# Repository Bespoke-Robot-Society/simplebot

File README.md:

# SimpleBot

Bespoke Robot Society's original design for kids, students, or cost-sensitive tinkerers.

Goals:

* Control a basic, multipurpose teaching robot with the Pi Pico (or Pico W).
* Demonstrate **optical odometry** - measuring the distance wheels turn by counting pulses on light sensors.
* Demonstrate **line following** - steer the robot in response to reflectance sensors that give the position of the line.
* Leave pins open on the microcontroller for additional upgrades.
* **Do not exceed $20 in price, with batteries included.**

## Hardware

Simplebot is based on the "Arduino Smart Car" kit that can be found on Amazon or Aliexpress. This provides a caster wheel, two yellow "TT" motors with optical encoder wheels and actual wheels, a power switch, and a 4xAA battery case. (~$6)

For line detectors, a generic "Infrared Obstacle Avoidance Sensor" module can be found in the US for 20 for $10 - SimpleBot requires two ($1).

Microcontroller - Raspberry Pi Pico ($4) or Raspberry Pi Pico W ($6).

Motor Controller - The TB6612FNG dual H-bridge module. You might be able to find this for $1 or less from overseas, but 3 for $9 is available in the US. ($3)

The optical encoder module requires one LED, one photoresistor, five resistors, and one LM393 chip for both. I don't know the prices for these, as I had them on hand.

an MPU6050 (Accelerometer/gyroscope) and nRF24l01 (2.4GHz radio module) are included on the circuit board, but haven't been tested or programmed yet. These occupy the I2C and SPI buses respectively, and would play well with some additional sensors (at the cost of spare pins for more SPI devices).

## Circuit Board

A through-hole (THT) PCB design is available for easy assembly.

The PCB integrates:
- Raspberry Pi Pico microcontroller (or compatible)
- TB6612FNG motor driver (or external H-bridge support)
- Buck converter for power regulation
- LM393-based optical encoder circuit
- Headers for nRF24L01 radio and MPU6050 IMU
- 4 sensor headers for expansion
- Analog and digital GPIO breakouts

See [PCB_GUIDE.md](PCB_GUIDE.md) for detailed PCB documentation.

See [ASSEMBLY_GUIDE.md](ASSEMBLY_GUIDE.md) for mechanical assembly instructions. 

## Software

Copy the included files to your Pi Pico by USB cable. I used Thonny to test the robot's programs.

# Future Work

Should I switch to an off-the-shelf optical encoder module, or should I build a custom line detecting sensor?

Printed circuit boards:

* Through hole soldering kit
* a board-on-board PCB - same layout as the protoboard, but soldered flat together.
* a custom PCB that uses the ICs from the modules directly

SimpleBot is unfortunately too large for standard micromouse mazes, so a "simplebot mini" seems to be in order.

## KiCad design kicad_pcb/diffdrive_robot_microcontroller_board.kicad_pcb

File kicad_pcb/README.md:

Pico library: KiCad-RP-Pico-main

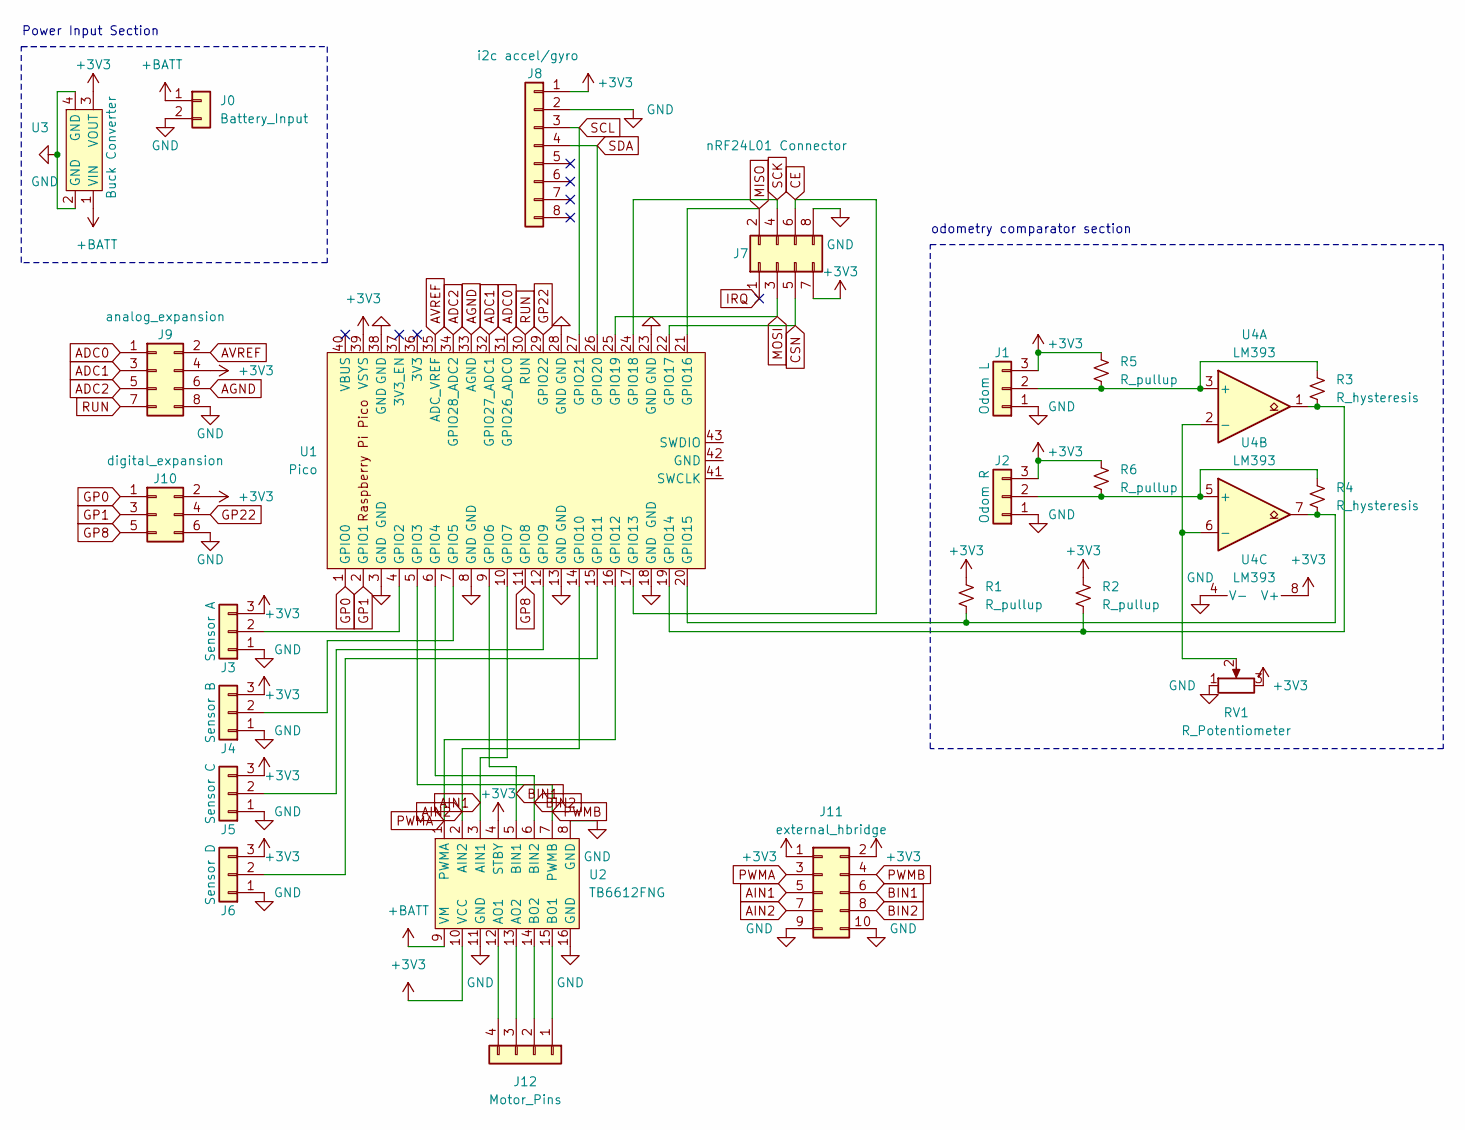
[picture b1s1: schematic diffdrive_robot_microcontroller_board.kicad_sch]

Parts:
J0: Battery_Input; PinSocket_1x02_P2.54mm_Vertical
J1: Odom L; PinHeader_1x03_P2.54mm_Vertical
J2: Odom R; PinHeader_1x03_P2.54mm_Vertical
J3: Sensor A; PinHeader_1x03_P2.54mm_Vertical
J4: Sensor B; PinHeader_1x03_P2.54mm_Vertical
J5: Sensor C; PinHeader_1x03_P2.54mm_Vertical
J6: Sensor D; PinHeader_1x03_P2.54mm_Vertical
J7: nRF24L01 Connector; PinSocket_2x04_P2.54mm_Vertical
J8: i2c accel/gyro; PinSocket_1x08_P2.54mm_Vertical
J9: analog_expansion; PinSocket_2x04_P2.54mm_Vertical
J10: digital_expansion; PinSocket_2x03_P2.54mm_Vertical
J11: external_hbridge; PinSocket_2x05_P2.54mm_Vertical
J12: Motor_Pins; PinSocket_1x04_P2.54mm_Vertical
R1, R2, R5, R6: R_pullup; R_Axial_DIN0207_L6.3mm_D2.5mm_P7.62mm_Horizontal
R3, R4: R_hysteresis; R_Axial_DIN0207_L6.3mm_D2.5mm_P7.62mm_Horizontal
RV1: R_Potentiometer; PinHeader_1x03_P2.54mm_Vertical
U1: Pico; RPi_Pico_SMD_TH
U2: TB6612FNG; TB6612FNG_Breakout
U3: Buck Converter; BuckConverter_Breakout
U4: LM393; DIP-8_W7.62mm_Socket

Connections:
+3V3: J1.3, J2.3, J3.3, J4.3, J5.3, J6.3, J7.7, J8.1, J9.4, J10.2, J11.1, J11.2, R1.1, R2.1, R5.1, R6.1, RV1.3, U1.39 (VSYS), U2.4 (STBY), U2.10 (VCC), U3.3 (VOUT), U4.8 (V+)
+BATT: J0.1, U2.9 (VM), U3.1 (VIN)
ADC0: J9.1, U1.31 (GPIO26_ADC0)
ADC1: J9.3, U1.32 (GPIO27_ADC1)
ADC2: J9.5, U1.34 (GPIO28_ADC2)
AGND: J9.6, U1.33 (AGND)
AIN1: J11.5, U1.10 (GPIO7), U2.3 (AIN1)
AIN2: J11.7, U1.14 (GPIO10), U2.2 (AIN2)
AVREF: J9.2, U1.35 (ADC_VREF)
BIN1: J11.6, U1.9 (GPIO6), U2.5 (BIN1)
BIN2: J11.8, U1.6 (GPIO4), U2.6 (BIN2)
CE: J7.6, U1.17 (GPIO13)
CSN: J7.5, U1.22 (GPIO17)
GND: J0.2, J1.1, J2.1, J3.1, J4.1, J5.1, J6.1, J7.8, J8.2, J9.8, J10.6, J11.9, J11.10, RV1.1, U1.3 (GND), U1.8 (GND), U1.13 (GND), U1.18 (GND), U1.23 (GND), U1.28 (GND), U1.38 (GND), U2.8 (GND), U2.11 (GND), U2.16 (GND), U3.2 (GND), U3.4 (GND), U4.4 (V-)
GP0: J10.1, U1.1 (GPIO0)
GP1: J10.3, U1.2 (GPIO1)
GP8: J10.5, U1.11 (GPIO8)
GP22: J10.4, U1.29 (GPIO22)
IRQ: J7.1
MISO: J7.2, U1.21 (GPIO16)
MOSI: J7.3, U1.25 (GPIO19)
unnamed: J1.2, R3.2, R5.2, U4.3 (+)
unnamed: J3.2, U1.4 (GPIO2)
unnamed: J4.2, U1.7 (GPIO5)
unnamed: J5.2, U1.12 (GPIO9)
unnamed: J6.2, U1.15 (GPIO11)
unnamed: R1.2, R4.2, U1.20 (GPIO15), U4.7
unnamed: J12.4, U2.12 (AO1)
unnamed: J12.3, U2.13 (AO2)
unnamed: J12.2, U2.14 (BO2)
unnamed: J12.1, U2.15 (BO1)
unnamed: R2.2, R3.1, U1.19 (GPIO14), U4.1
unnamed: RV1.2, U4.2 (-), U4.6 (-)
unnamed: J2.2, R4.1, R6.2, U4.5 (+)
PWMA: J11.3, U1.16 (GPIO12), U2.1 (PWMA)
PWMB: J11.4, U1.5 (GPIO3), U2.7 (PWMB)
RUN: J9.7, U1.30 (RUN)
SCK: J7.4, U1.24 (GPIO18)
SCL: J8.3, U1.27 (GPIO21)
SDA: J8.4, U1.26 (GPIO20)

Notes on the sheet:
odometry comparator section
Power Input Section

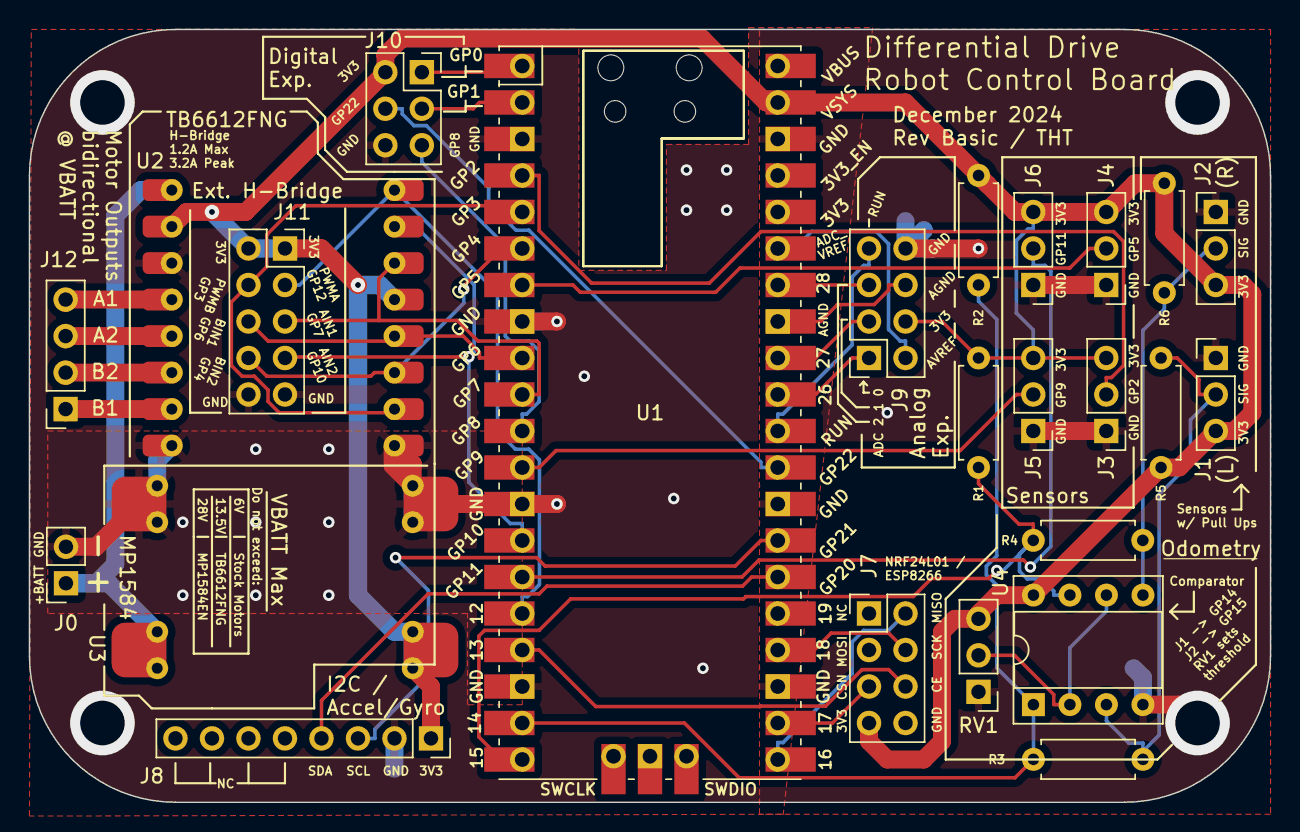
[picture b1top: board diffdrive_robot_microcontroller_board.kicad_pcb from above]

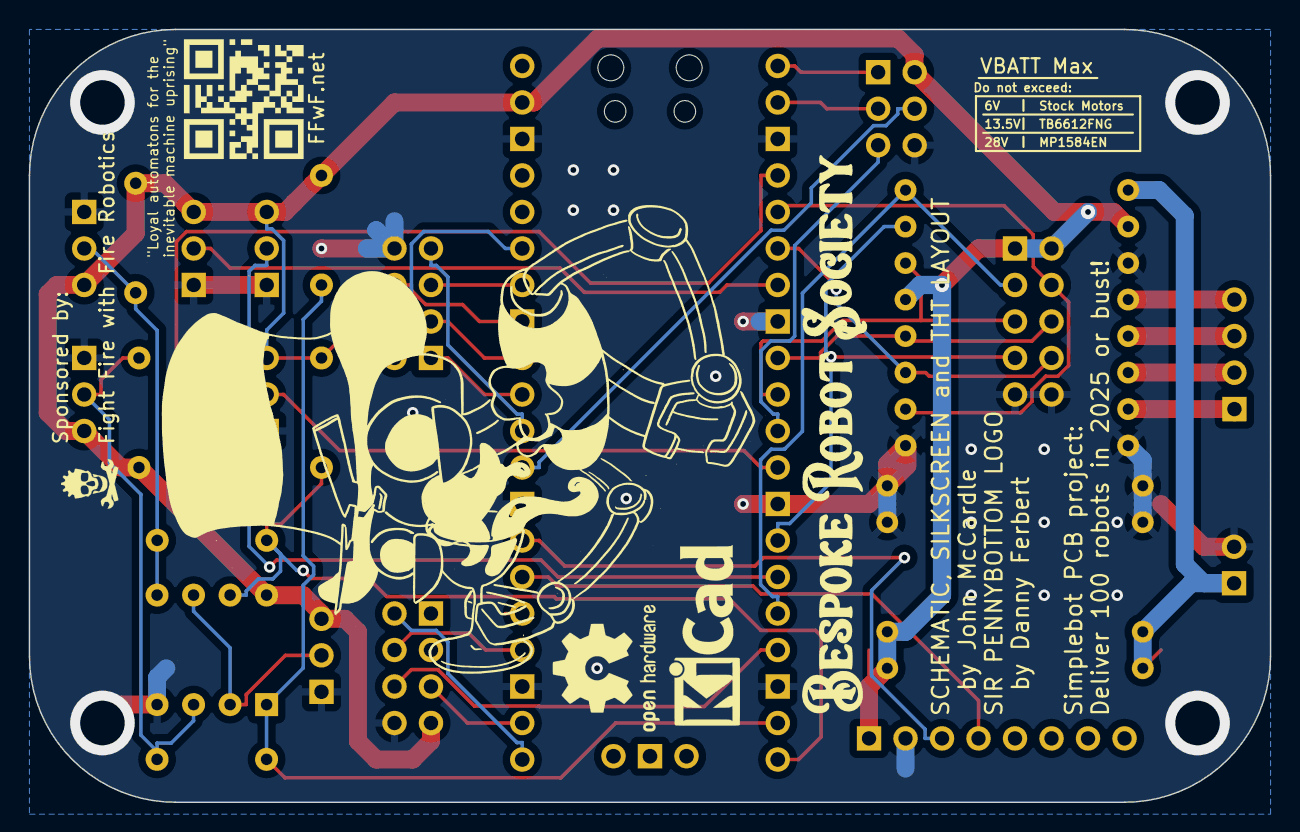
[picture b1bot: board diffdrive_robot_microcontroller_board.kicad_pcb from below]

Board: 2 copper layers, 86.4 x 53.8 mm, 26 parts (3 on the bottom side), 39 nets.

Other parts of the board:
G1: LOGO; BRS_LOGO
G2: LOGO; BRS_TEXT

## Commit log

2024-12-26 Initial (THT) board designs, autorouted with freerouting-2.0.1
2025-10-11 August through October 2025 CAD revisions
2025-10-11 Docs update
